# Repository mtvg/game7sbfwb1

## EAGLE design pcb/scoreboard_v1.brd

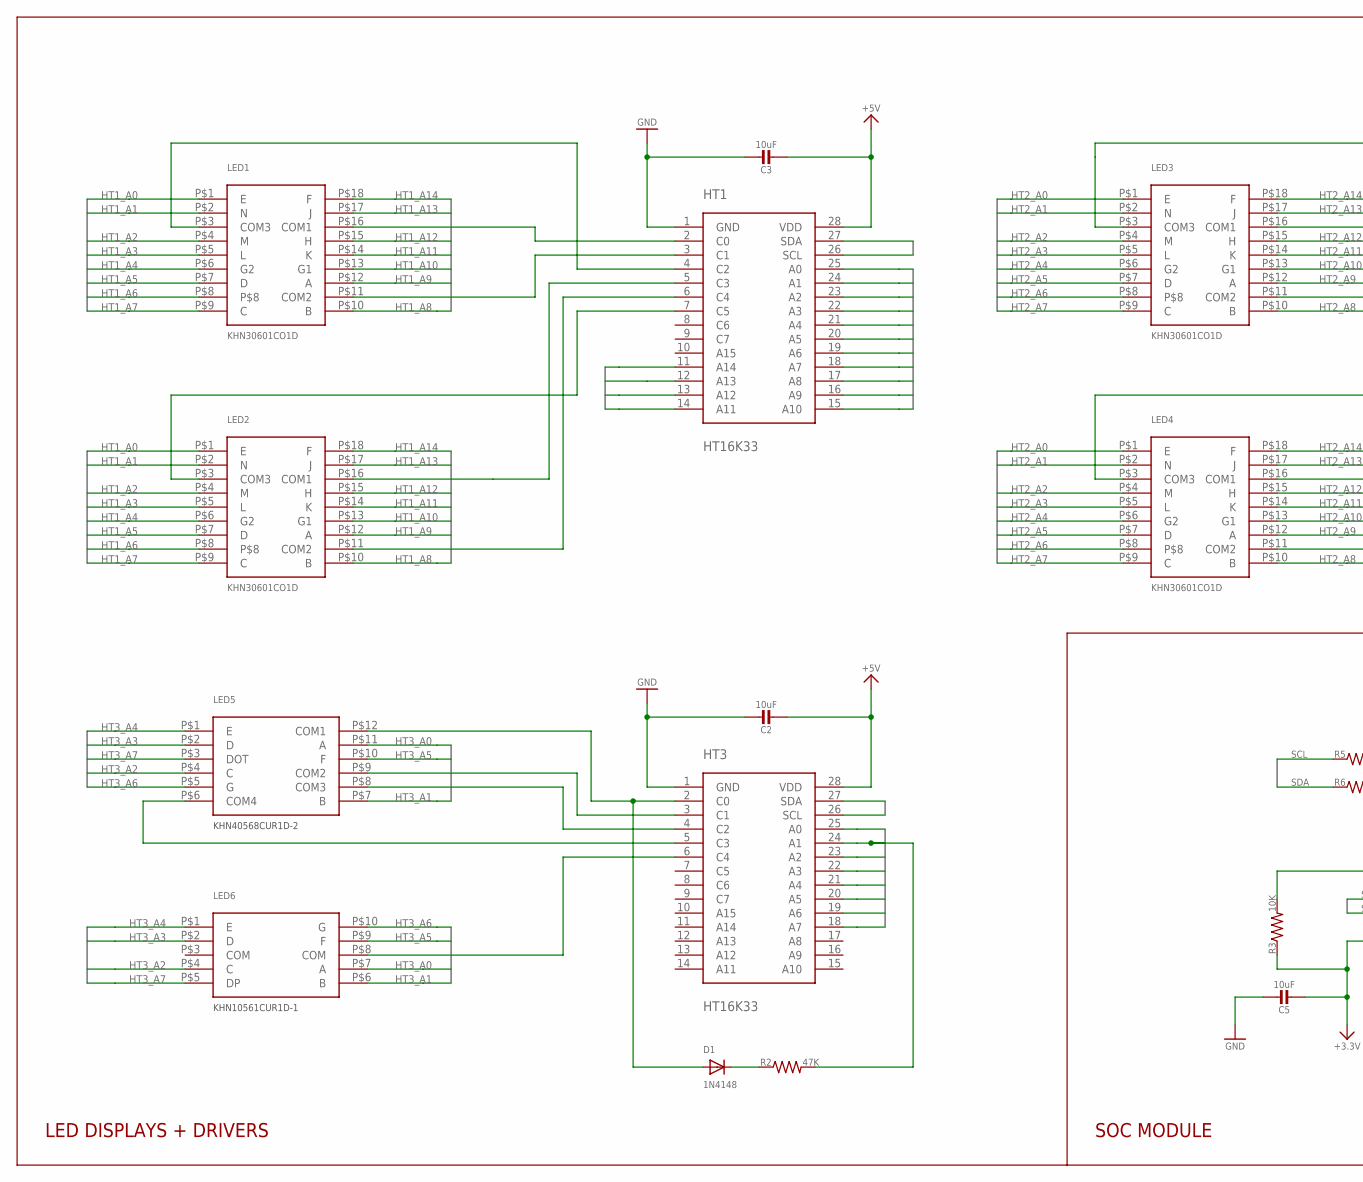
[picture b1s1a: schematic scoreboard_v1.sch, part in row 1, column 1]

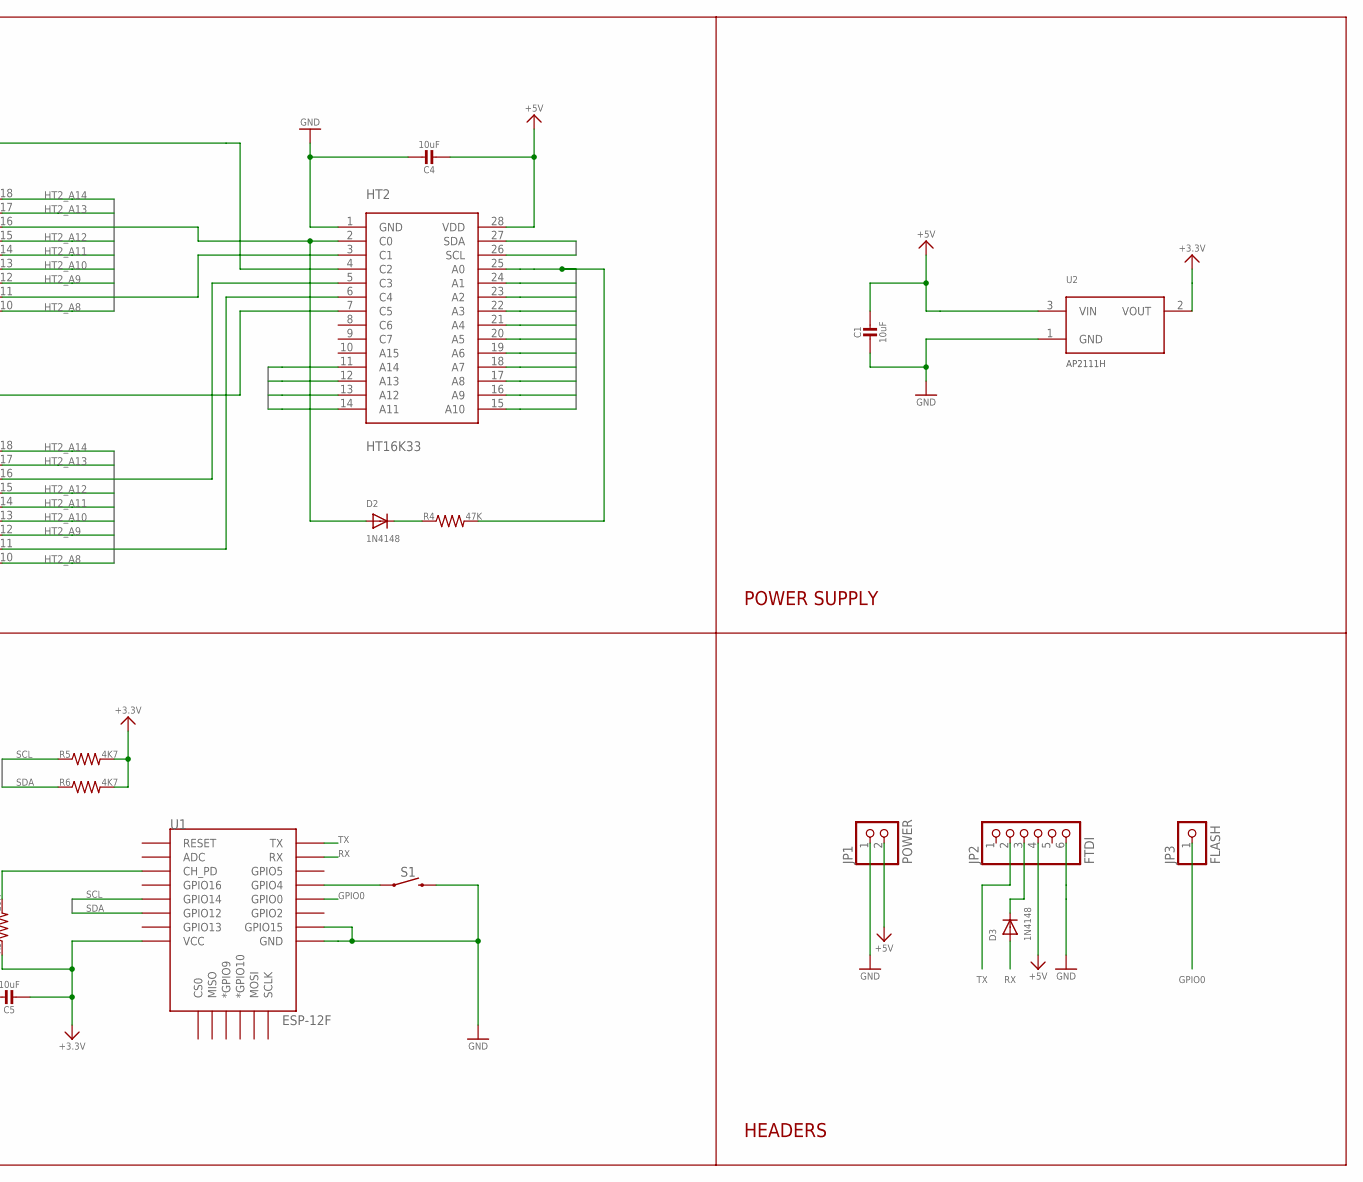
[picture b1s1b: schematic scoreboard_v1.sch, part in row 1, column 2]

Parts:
C1, C2, C3, C4, C5: 10uF; _1206
D1, D2, D3: 1N4148; SOD-123
HT1, HT2, HT3: HT16K33; SOP28
JP1: POWER; 1X02
JP2: FTDI; 1X06
JP3: FLASH; 1X01
LED1, LED2, LED3, LED4: KHN30601CO1D
LED5: KHN40568CUR1D-2
LED6: KHN10561CUR1D-1
R2, R4: 47K; R1206
R3: 10K; R1206
R5, R6: 4K7; R1206
S1: MOMENTARY-SWITCH-SPST-PTH-6.0MM; TACTILE_SWITCH_PTH_6.0MM
U1: ESP-12F; ESP12E-SMD
U2: AP2111H; SOT223

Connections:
3.3V: C5.2, R3.1, R5.2, R6.2, U1.VCC, U2.2 (VOUT)
+5V: C1.1, C2.2, C3.2, C4.2, HT1.28 (VDD), HT2.28 (VDD), HT3.28 (VDD), JP1.2, JP2.4, U2.3 (VIN)
GND: C1.2, C2.1, C3.1, C4.1, C5.1, HT1.1 (GND), HT2.1 (GND), HT3.1 (GND), JP1.1, JP2.6, S1.3 (2), U1.GND, U1.GPIO15, U2.1 (GND)
GPIO0: JP3.1, U1.GPIO0
HT1_A0: HT1.25 (A0), LED1.P$1 (E), LED2.P$1 (E)
HT1_A1: HT1.24 (A1), LED1.P$2 (N), LED2.P$2 (N)
HT1_A2: HT1.23 (A2), LED1.P$4 (M), LED2.P$4 (M)
HT1_A3: HT1.22 (A3), LED1.P$5 (L), LED2.P$5 (L)
HT1_A4: HT1.21 (A4), LED1.P$6 (G2), LED2.P$6 (G2)
HT1_A5: HT1.20 (A5), LED1.P$7 (D), LED2.P$7 (D)
HT1_A6: HT1.19 (A6), LED1.P$8, LED2.P$8
HT1_A7: HT1.18 (A7), LED1.P$9 (C), LED2.P$9 (C)
HT1_A8: HT1.17 (A8), LED1.P$10 (B), LED2.P$10 (B)
HT1_A9: HT1.16 (A9), LED1.P$12 (A), LED2.P$12 (A)
HT1_A10: HT1.15 (A10), LED1.P$13 (G1), LED2.P$13 (G1)
HT1_A11: HT1.14 (A11), LED1.P$14 (K), LED2.P$14 (K)
HT1_A12: HT1.13 (A12), LED1.P$15 (H), LED2.P$15 (H)
HT1_A13: HT1.12 (A13), LED1.P$17 (J), LED2.P$17 (J)
HT1_A14: HT1.11 (A14), LED1.P$18 (F), LED2.P$18 (F)
HT1_C0: HT1.2 (C0), LED1.P$16 (COM1)
HT1_C1: HT1.3 (C1), LED1.P$11 (COM2)
HT1_C2: HT1.4 (C2), LED1.P$3 (COM3)
HT1_C3: HT1.5 (C3), LED2.P$16 (COM1)
HT1_C4: HT1.6 (C4), LED2.P$11 (COM2)
HT1_C5: HT1.7 (C5), LED2.P$3 (COM3)
HT2_A0: HT2.25 (A0), LED3.P$1 (E), LED4.P$1 (E), R4.2
HT2_A1: HT2.24 (A1), LED3.P$2 (N), LED4.P$2 (N)
HT2_A2: HT2.23 (A2), LED3.P$4 (M), LED4.P$4 (M)
HT2_A3: HT2.22 (A3), LED3.P$5 (L), LED4.P$5 (L)
HT2_A4: HT2.21 (A4), LED3.P$6 (G2), LED4.P$6 (G2)
HT2_A5: HT2.20 (A5), LED3.P$7 (D), LED4.P$7 (D)
HT2_A6: HT2.19 (A6), LED3.P$8, LED4.P$8
HT2_A7: HT2.18 (A7), LED3.P$9 (C), LED4.P$9 (C)
HT2_A8: HT2.17 (A8), LED3.P$10 (B), LED4.P$10 (B)
HT2_A9: HT2.16 (A9), LED3.P$12 (A), LED4.P$12 (A)
HT2_A10: HT2.15 (A10), LED3.P$13 (G1), LED4.P$13 (G1)
HT2_A11: HT2.14 (A11), LED3.P$14 (K), LED4.P$14 (K)
HT2_A12: HT2.13 (A12), LED3.P$15 (H), LED4.P$15 (H)
HT2_A13: HT2.12 (A13), LED3.P$17 (J), LED4.P$17 (J)
HT2_A14: HT2.11 (A14), LED3.P$18 (F), LED4.P$18 (F)
HT2_C0: D2.A, HT2.2 (C0), LED3.P$16 (COM1)
HT2_C1: HT2.3 (C1), LED3.P$11 (COM2)
HT2_C2: HT2.4 (C2), LED3.P$3 (COM3)
HT2_C3: HT2.5 (C3), LED4.P$16 (COM1)
HT2_C4: HT2.6 (C4), LED4.P$11 (COM2)
HT2_C5: HT2.7 (C5), LED4.P$3 (COM3)
HT3_A0: HT3.25 (A0), LED5.P$11 (A), LED6.P$7 (A)
HT3_A1: HT3.24 (A1), LED5.P$7 (B), LED6.P$6 (B), R2.2
HT3_A2: HT3.23 (A2), LED5.P$4 (C), LED6.P$4 (C)
HT3_A3: HT3.22 (A3), LED5.P$2 (D), LED6.P$2 (D)
HT3_A4: HT3.21 (A4), LED5.P$1 (E), LED6.P$1 (E)
HT3_A5: HT3.20 (A5), LED5.P$10 (F), LED6.P$9 (F)
HT3_A6: HT3.19 (A6), LED5.P$5 (G), LED6.P$10 (G)
HT3_A7: HT3.18 (A7), LED5.P$3 (DOT), LED6.P$5 (DP)
HT3_C0: D1.A, HT3.2 (C0), LED5.P$12 (COM1)
HT3_C1: HT3.3 (C1), LED5.P$9 (COM2)
HT3_C2: HT3.4 (C2), LED5.P$8 (COM3)
HT3_C3: HT3.5 (C3), LED5.P$6 (COM4)
HT3_C4: HT3.6 (C4), LED6.P$8 (COM)
unnamed: S1.1, U1.GPIO4
unnamed: D3.C, JP2.3
unnamed: D1.C, R2.1
unnamed: R3.2, U1.CH_PD
unnamed: D2.C, R4.1
RX: D3.A, U1.RXD0 (RX)
SCL: HT1.26 (SCL), HT2.26 (SCL), HT3.26 (SCL), R5.1, U1.GPIO14
SDA: HT1.27 (SDA), HT2.27 (SDA), HT3.27 (SDA), R6.1, U1.GPIO12
TX: JP2.2, U1.TXD0 (TX)

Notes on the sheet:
LED DISPLAYS + DRIVERS
POWER SUPPLY
HEADERS
SOC MODULE

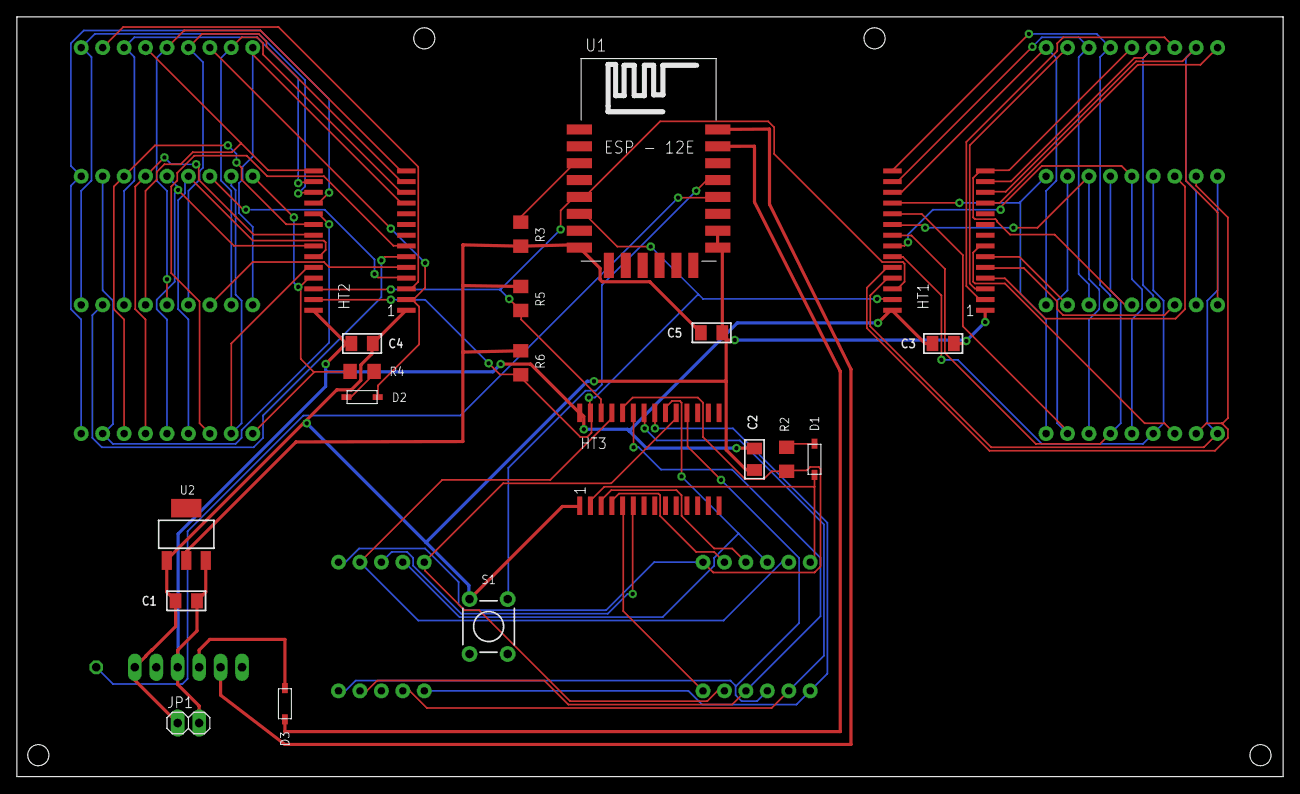
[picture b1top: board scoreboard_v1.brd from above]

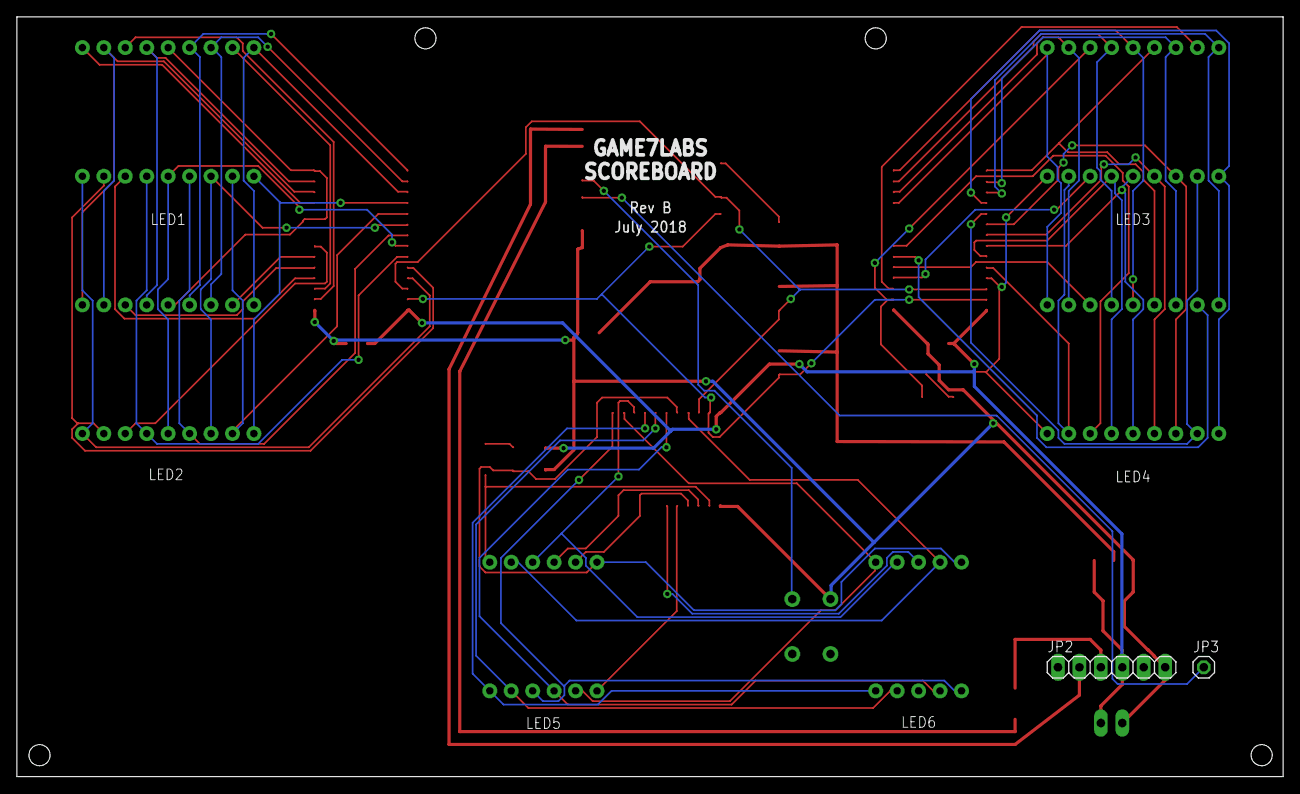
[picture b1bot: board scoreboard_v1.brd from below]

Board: 2 copper layers, 150.0 x 90.0 mm, 28 parts (8 on the bottom side), 68 nets.

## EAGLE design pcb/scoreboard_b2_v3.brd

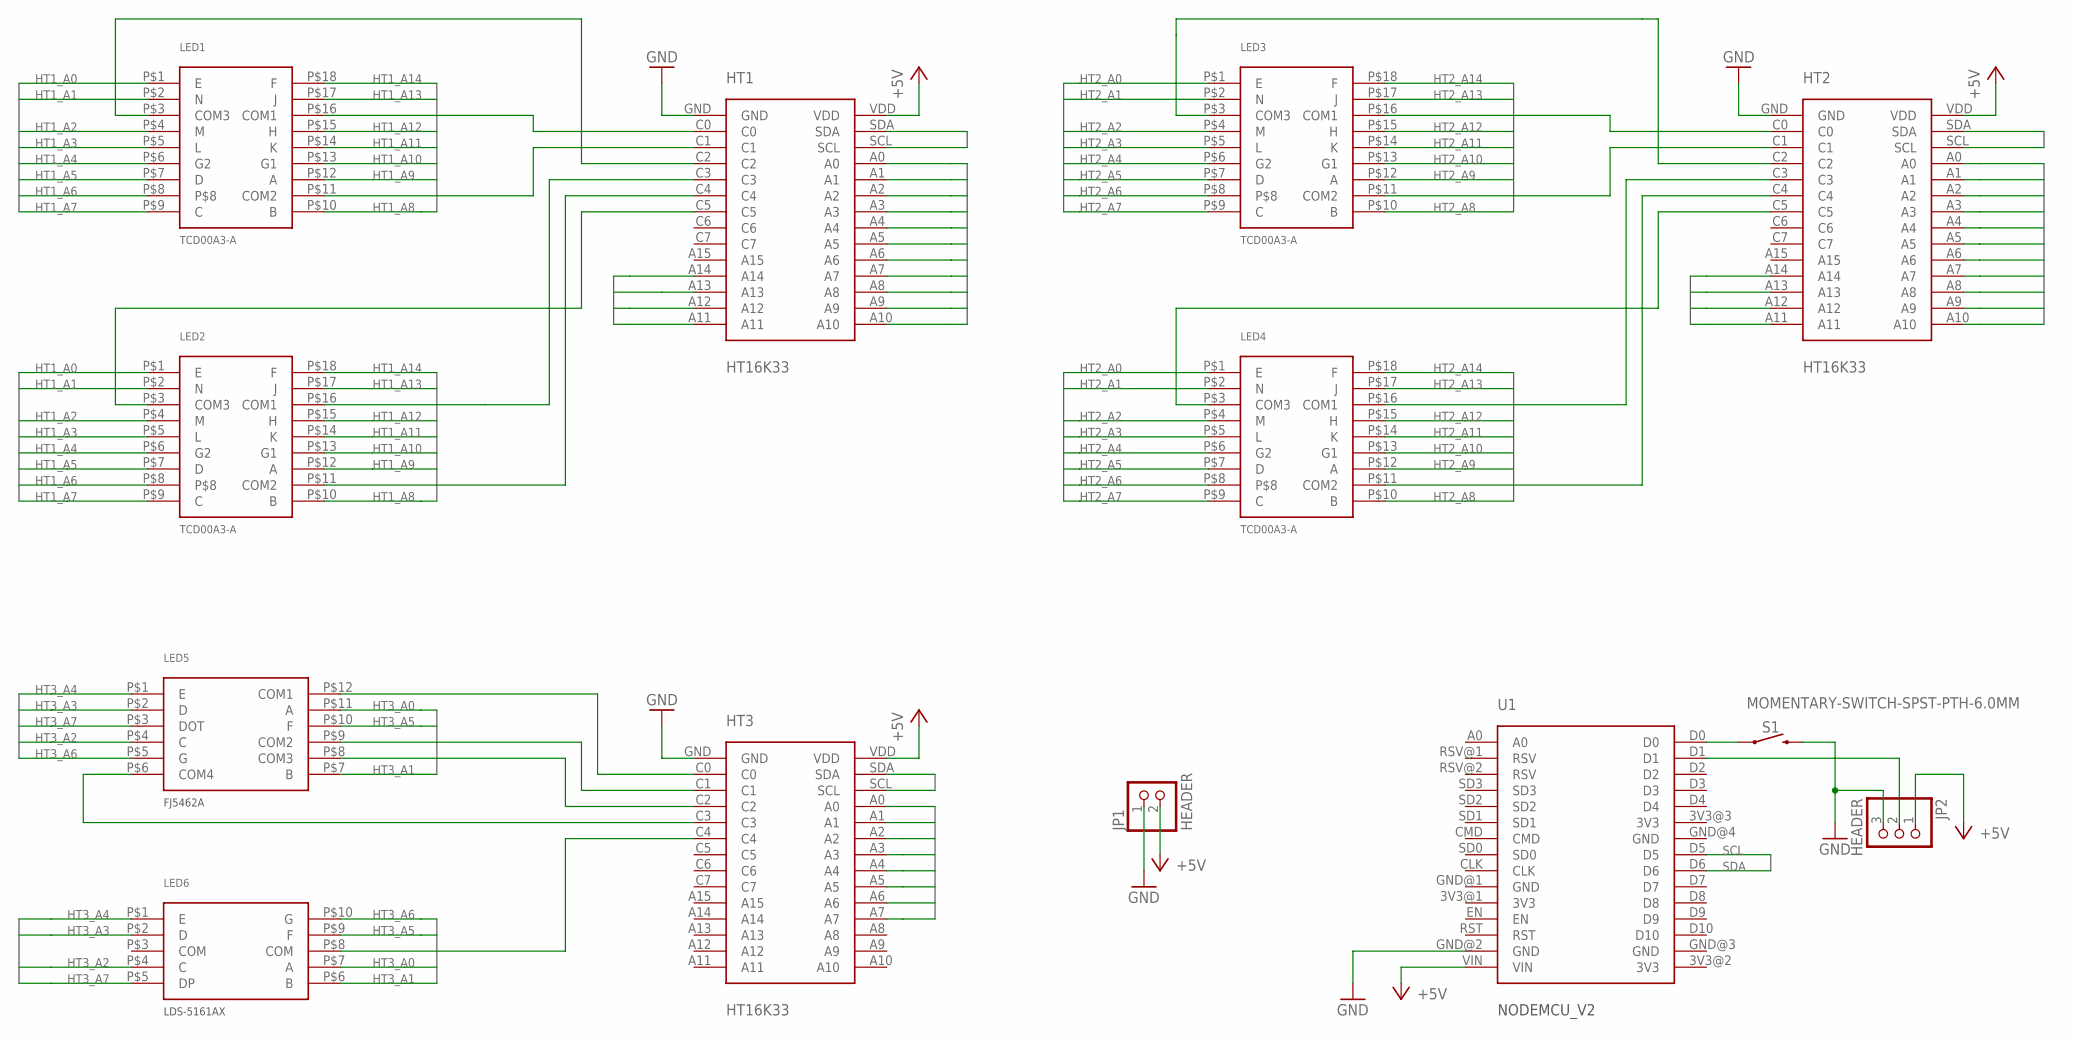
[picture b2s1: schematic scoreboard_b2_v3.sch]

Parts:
HT1, HT2, HT3: HT16K33
JP1: HEADER; 1X02
JP2: HEADER; 1X03
LED1, LED2, LED3, LED4: TCD00A3-A
LED5: FJ5462A
LED6: LDS-5161AX
S1: MOMENTARY-SWITCH-SPST-PTH-6.0MM; TACTILE_SWITCH_PTH_6.0MM
U1: NODEMCU_V2

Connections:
+5V: HT1.VDD, HT2.VDD, HT3.VDD, JP1.2, JP2.1, U1.VIN
BUZ: JP2.2, U1.D1
GND: HT1.GND, HT2.GND, HT3.GND, JP1.1, JP2.3, S1.3 (2), U1.GND@2 (GND)
HT1_A0: HT1.A0, LED1.P$1 (E), LED2.P$1 (E)
HT1_A1: HT1.A1, LED1.P$2 (N), LED2.P$2 (N)
HT1_A2: HT1.A2, LED1.P$4 (M), LED2.P$4 (M)
HT1_A3: HT1.A3, LED1.P$5 (L), LED2.P$5 (L)
HT1_A4: HT1.A4, LED1.P$6 (G2), LED2.P$6 (G2)
HT1_A5: HT1.A5, LED1.P$7 (D), LED2.P$7 (D)
HT1_A6: HT1.A6, LED1.P$8, LED2.P$8
HT1_A7: HT1.A7, LED1.P$9 (C), LED2.P$9 (C)
HT1_A8: HT1.A8, LED1.P$10 (B), LED2.P$10 (B)
HT1_A9: HT1.A9, LED1.P$12 (A), LED2.P$12 (A)
HT1_A10: HT1.A10, LED1.P$13 (G1), LED2.P$13 (G1)
HT1_A11: HT1.A11, LED1.P$14 (K), LED2.P$14 (K)
HT1_A12: HT1.A12, LED1.P$15 (H), LED2.P$15 (H)
HT1_A13: HT1.A13, LED1.P$17 (J), LED2.P$17 (J)
HT1_A14: HT1.A14, LED1.P$18 (F), LED2.P$18 (F)
HT1_C0: HT1.C0, LED1.P$16 (COM1)
HT1_C1: HT1.C1, LED1.P$11 (COM2)
HT1_C2: HT1.C2, LED1.P$3 (COM3)
HT1_C3: HT1.C3, LED2.P$16 (COM1)
HT1_C4: HT1.C4, LED2.P$11 (COM2)
HT1_C5: HT1.C5, LED2.P$3 (COM3)
HT2_A0: HT2.A0, LED3.P$1 (E), LED4.P$1 (E)
HT2_A1: HT2.A1, LED3.P$2 (N), LED4.P$2 (N)
HT2_A2: HT2.A2, LED3.P$4 (M), LED4.P$4 (M)
HT2_A3: HT2.A3, LED3.P$5 (L), LED4.P$5 (L)
HT2_A4: HT2.A4, LED3.P$6 (G2), LED4.P$6 (G2)
HT2_A5: HT2.A5, LED3.P$7 (D), LED4.P$7 (D)
HT2_A6: HT2.A6, LED3.P$8, LED4.P$8
HT2_A7: HT2.A7, LED3.P$9 (C), LED4.P$9 (C)
HT2_A8: HT2.A8, LED3.P$10 (B), LED4.P$10 (B)
HT2_A9: HT2.A9, LED3.P$12 (A), LED4.P$12 (A)
HT2_A10: HT2.A10, LED3.P$13 (G1), LED4.P$13 (G1)
HT2_A11: HT2.A11, LED3.P$14 (K), LED4.P$14 (K)
HT2_A12: HT2.A12, LED3.P$15 (H), LED4.P$15 (H)
HT2_A13: HT2.A13, LED3.P$17 (J), LED4.P$17 (J)
HT2_A14: HT2.A14, LED3.P$18 (F), LED4.P$18 (F)
HT2_C0: HT2.C0, LED3.P$16 (COM1)
HT2_C1: HT2.C1, LED3.P$11 (COM2)
HT2_C2: HT2.C2, LED3.P$3 (COM3)
HT2_C3: HT2.C3, LED4.P$16 (COM1)
HT2_C4: HT2.C4, LED4.P$11 (COM2)
HT2_C5: HT2.C5, LED4.P$3 (COM3)
HT3_A0: HT3.A0, LED5.P$11 (A), LED6.P$7 (A)
HT3_A1: HT3.A1, LED5.P$7 (B), LED6.P$6 (B)
HT3_A2: HT3.A2, LED5.P$4 (C), LED6.P$4 (C)
HT3_A3: HT3.A3, LED5.P$2 (D), LED6.P$2 (D)
HT3_A4: HT3.A4, LED5.P$1 (E), LED6.P$1 (E)
HT3_A5: HT3.A5, LED5.P$10 (F), LED6.P$9 (F)
HT3_A6: HT3.A6, LED5.P$5 (G), LED6.P$10 (G)
HT3_A7: HT3.A7, LED5.P$3 (DOT), LED6.P$5 (DP)
HT3_C0: HT3.C0, LED5.P$12 (COM1)
HT3_C1: HT3.C1, LED5.P$9 (COM2)
HT3_C2: HT3.C2, LED5.P$8 (COM3)
HT3_C3: HT3.C3, LED5.P$6 (COM4)
HT3_C4: HT3.C4, LED6.P$8 (COM)
SCL: HT1.SCL, HT2.SCL, HT3.SCL, U1.D5
SDA: HT1.SDA, HT2.SDA, HT3.SDA, U1.D6
SW: S1.1, U1.D0

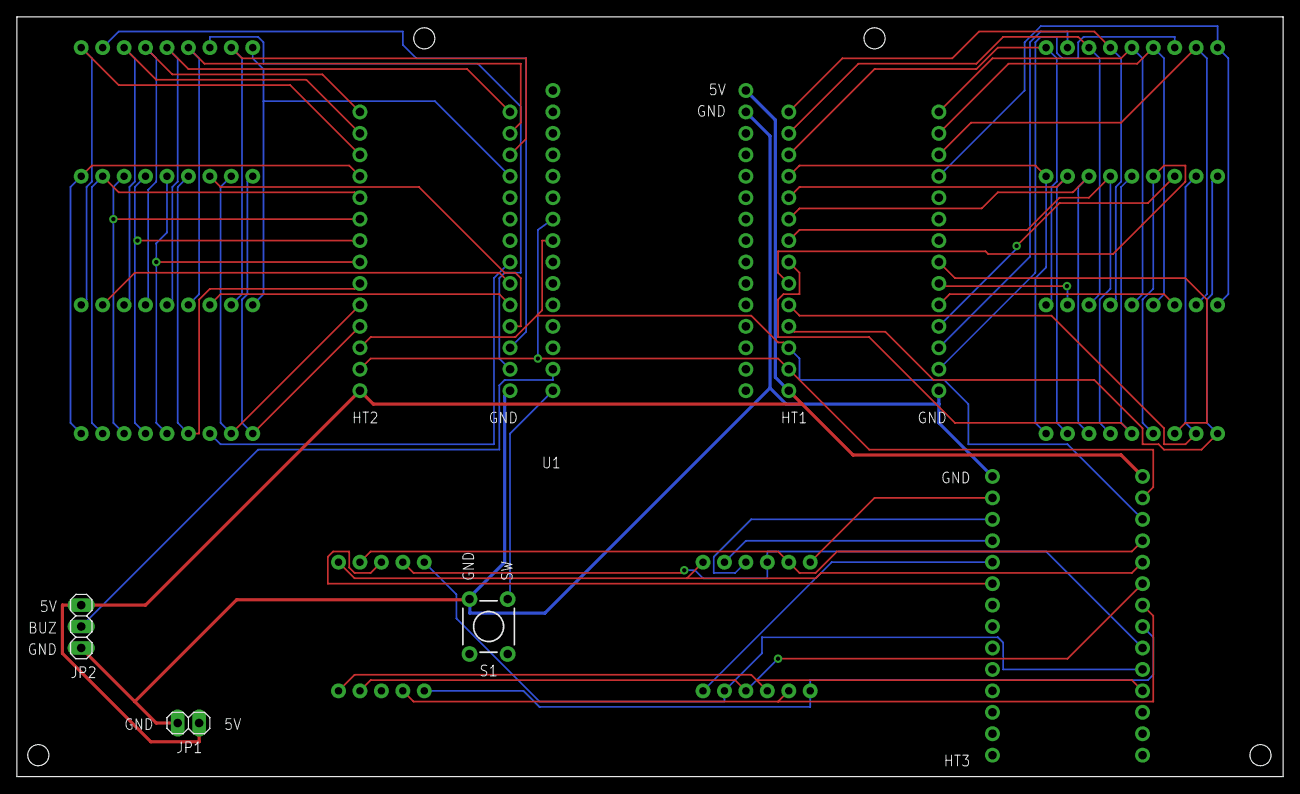
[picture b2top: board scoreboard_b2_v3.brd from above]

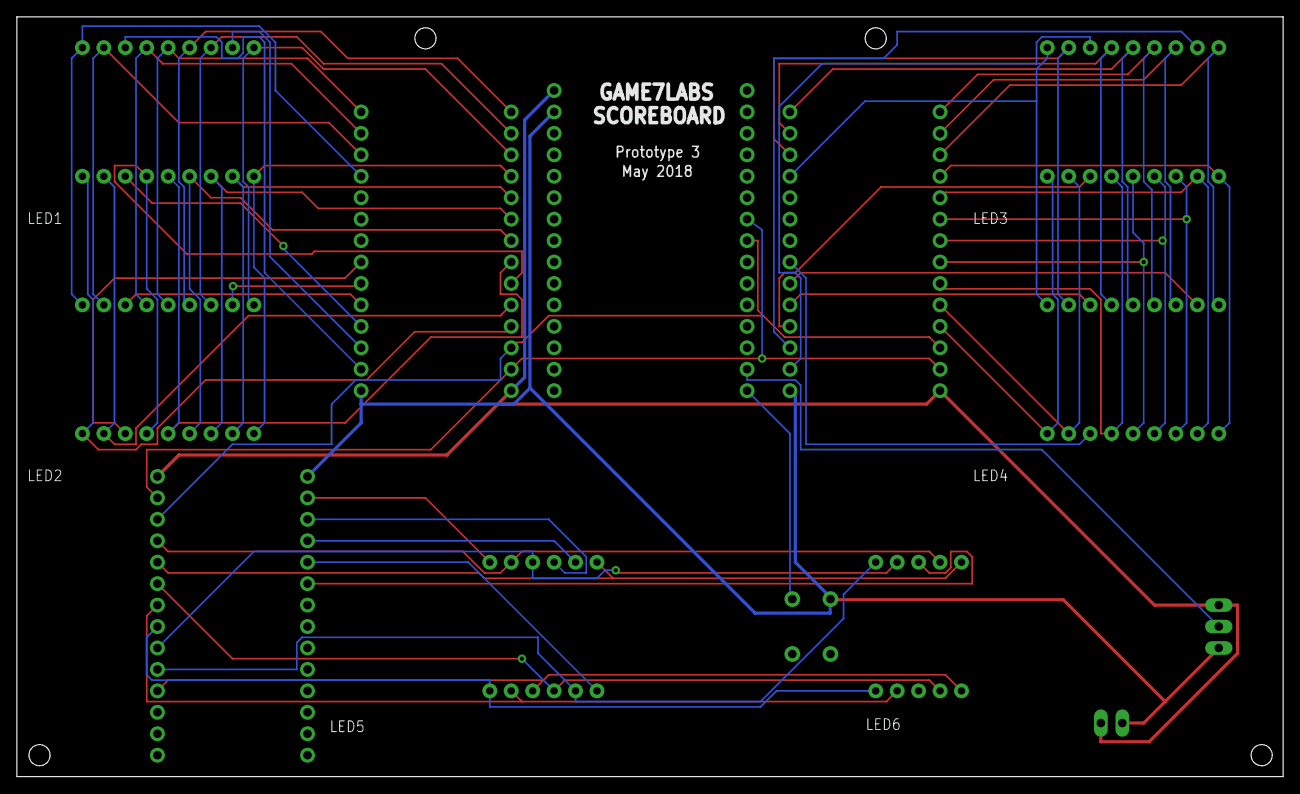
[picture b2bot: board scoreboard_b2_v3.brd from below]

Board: 2 copper layers, 150.0 x 90.0 mm, 13 parts (6 on the bottom side), 61 nets.

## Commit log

2018-05-03 project base
2018-05-03 Testing captive portal
2018-05-04 Added captive portal
2018-05-05 captive portal disconnect
2018-05-07 display digits
2018-05-07 iOS project added
2018-05-08 Added WS digest
2018-05-09 refactoring + set text display
2018-05-09 Firmware driver complete + swift example
2018-05-14 adding blink + buzzer
2018-06-02 Firmware update for prototype v3
2018-06-02 iOS update with NBA input
2018-06-02 led driver fw tab fix
2018-06-03 added game simulation
2018-06-04 Added iOS live NBA data
2018-06-08 PWM fix
2018-06-25 WNBA theScore data API
2018-07-05 Eagle files added
2018-07-22 Scoreboard PCB SMD
2018-07-24 PCB update for SMD version

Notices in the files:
parts and their libraries:
SparkFun-Switches: Licensing: Creative Commons ShareAlike 4.0 International - https://creativecommons.org/licenses/by-sa/4.0
